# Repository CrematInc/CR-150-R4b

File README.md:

# CR-150-R4b
KiCad files for Cremat's CR-150-R4b, an evaluation board for Cremat's charge sensitive preamplifier modules CR-11X
Includes Schematic, layout, and gerber files. Also a BOM.

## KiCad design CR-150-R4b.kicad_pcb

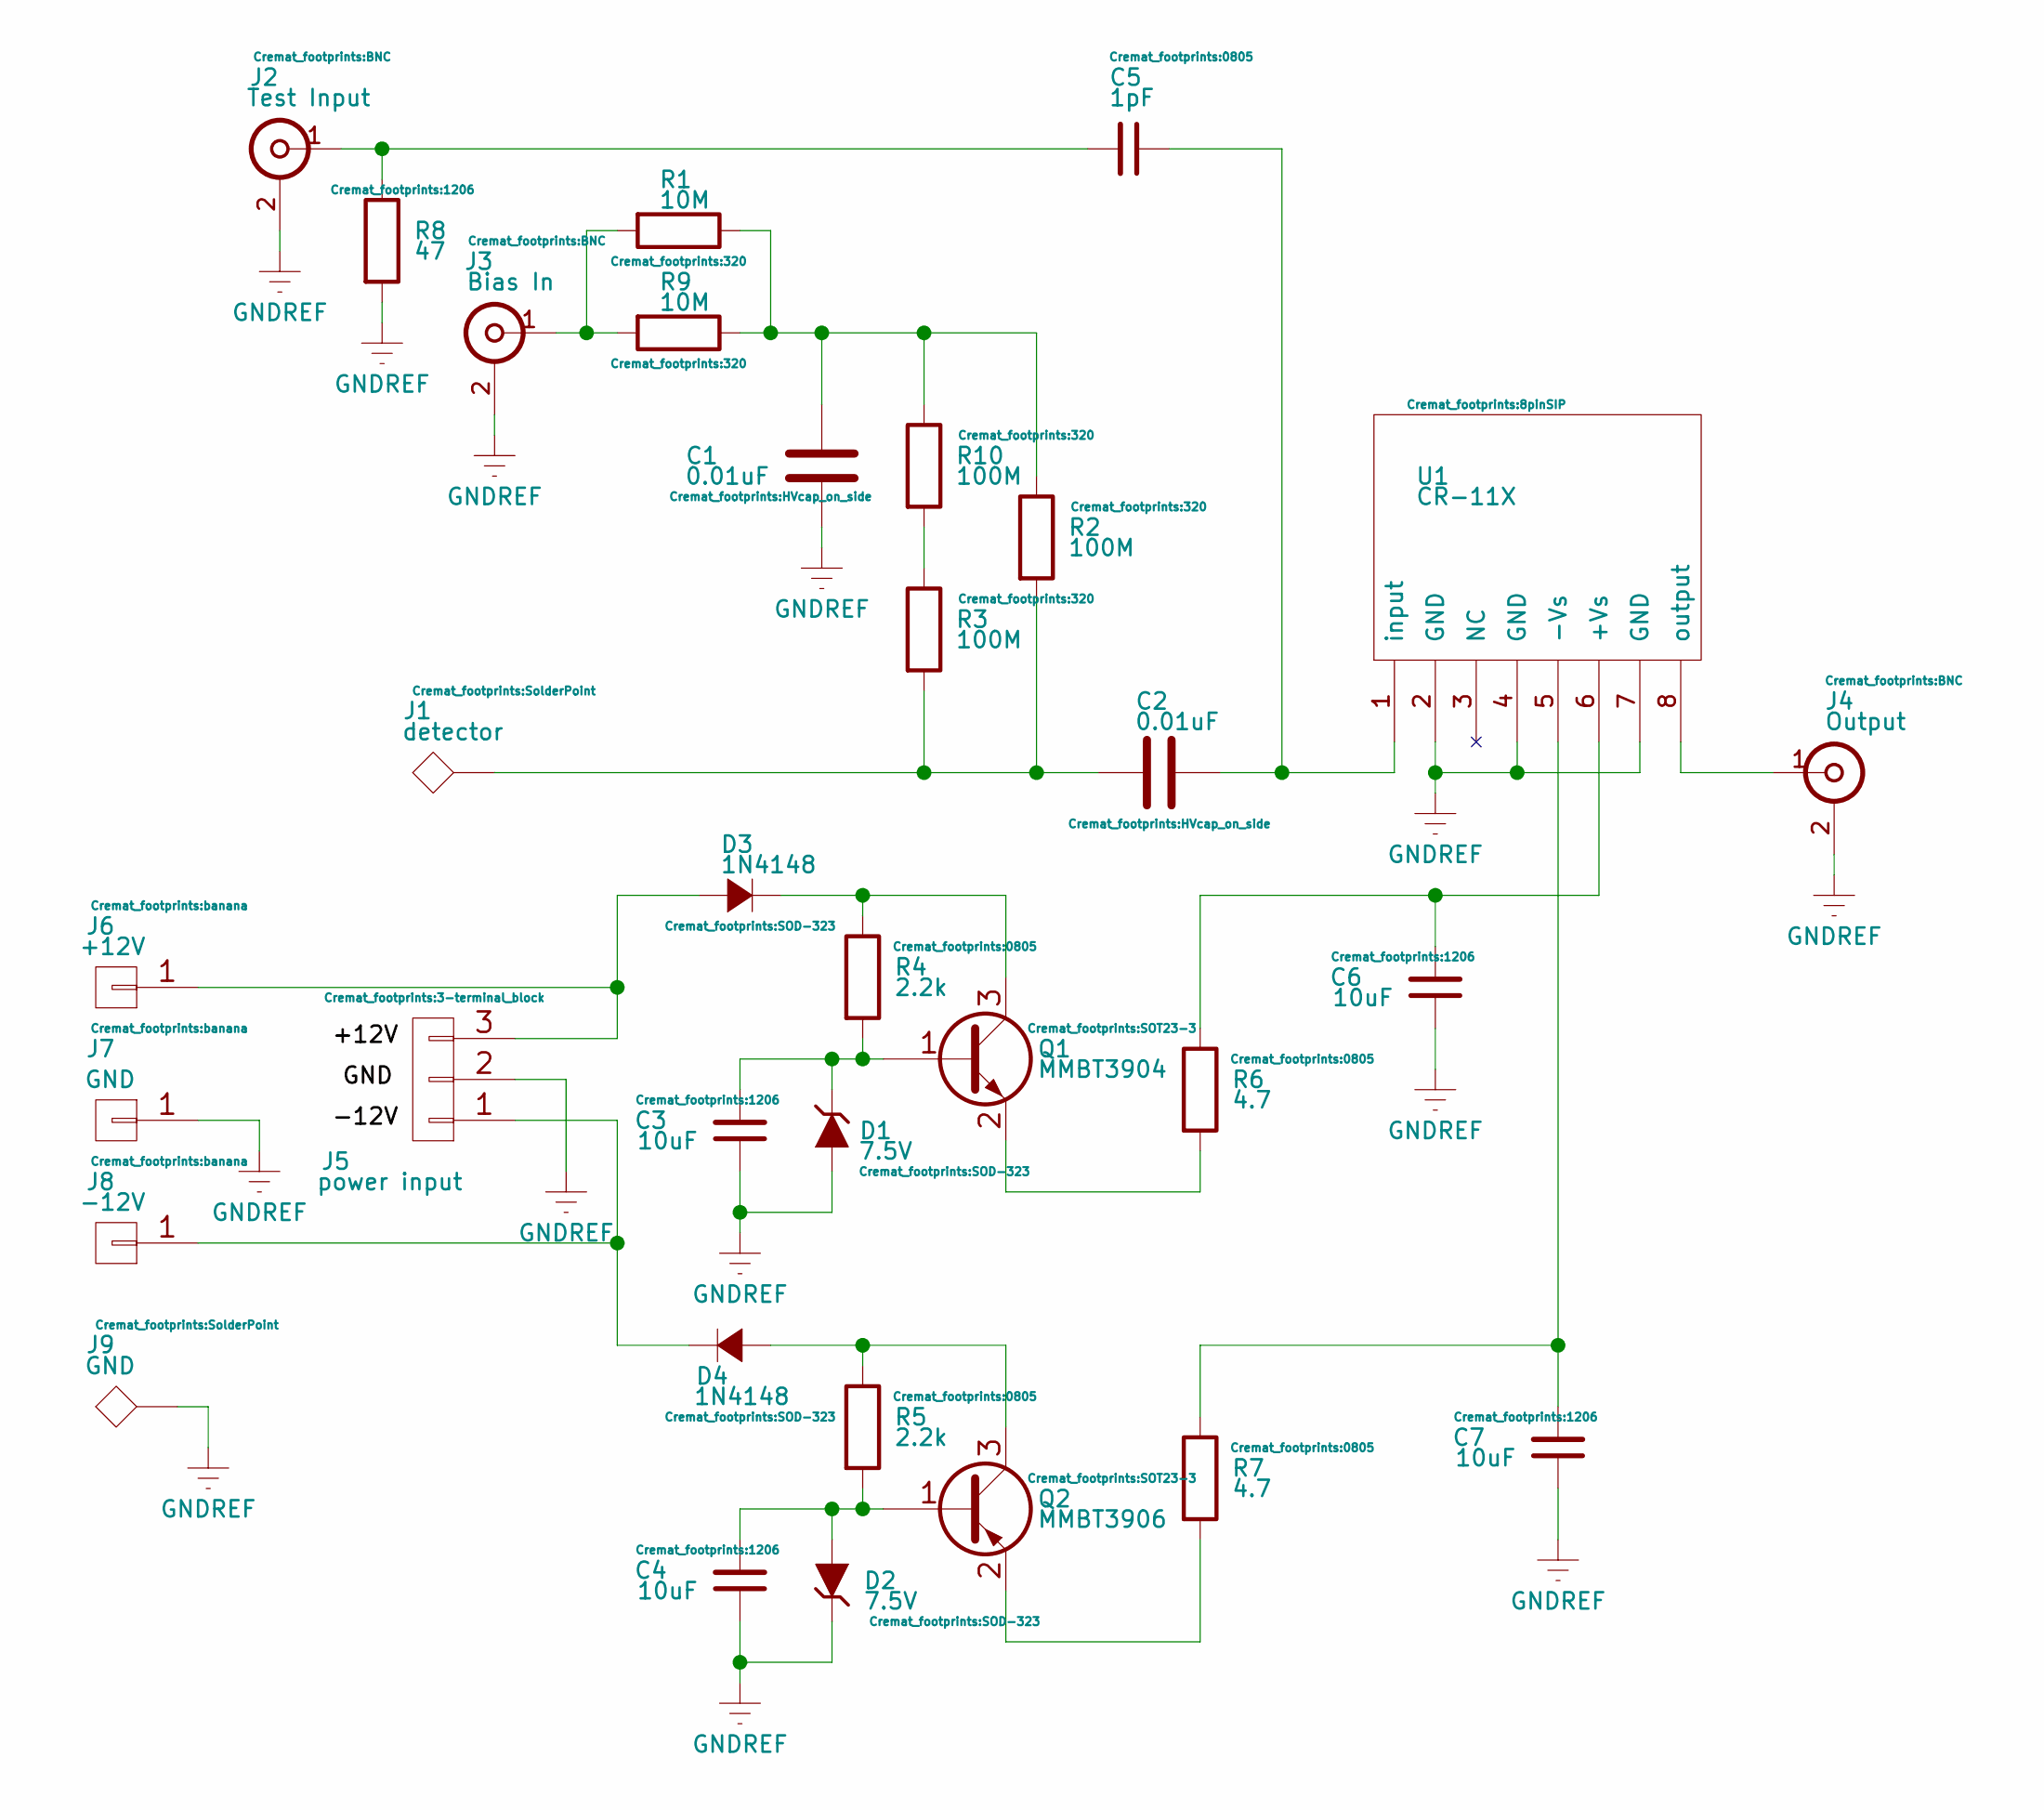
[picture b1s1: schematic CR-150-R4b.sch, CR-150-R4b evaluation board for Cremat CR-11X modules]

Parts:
C1, C2: 0.01uF; HVcap_on_side
C3, C4, C6, C7: 10uF; 1206
C5: 1pF; 0805
D1, D2: 7.5V; SOD-323
D3, D4: 1N4148; SOD-323
J1: detector; SolderPoint
J2: Test Input; BNC
J3: Bias In; BNC
J4: Output; BNC
J5: power input; 3-terminal_block
J6: +12V; banana
J7: GND; banana
J8: -12V; banana
J9: GND; SolderPoint
Q1: MMBT3904; SOT23-3
Q2: MMBT3906; SOT23-3
R1, R9: 10M; 320
R2, R3, R10: 100M; 320
R4, R5: 2.2k; 0805
R6, R7: 4.7; 0805
R8: 47; 1206
U1: CR-11X; 8pinSIP

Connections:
GNDREF: C1.1, C3.1, C4.1, C6.1, C7.1, D1.1 (A), D2.2 (K), J2.2 (Ext), J3.2 (Ext), J4.2 (Ext), J5.2, J7.1, J9.1, R8.2, U1.2 (GND), U1.4 (GND), U1.7 (GND)
unnamed: C1.2, R1.1, R2.1, R9.1, R10.1
unnamed: C2.1, J1.1, R2.2, R3.2
unnamed: C2.2, C5.1, U1.1 (input)
unnamed: C3.2, D1.2 (K), Q1.1 (B), R4.2
unnamed: C4.2, D2.1 (A), Q2.1 (B), R5.2
unnamed: C5.2, J2.1 (In), R8.1
unnamed: C6.2, R6.1, U1.6 (+Vs)
unnamed: C7.2, R7.1, U1.5 (-Vs)
unnamed: D3.1 (A), J5.3, J6.1
unnamed: D3.2 (C), Q1.3 (C), R4.1
unnamed: D4.1 (A), Q2.3 (C), R5.1
unnamed: D4.2 (C), J5.1, J8.1
unnamed: J3.1 (In), R1.2, R9.2
unnamed: J4.1 (In), U1.8 (output)
unnamed: Q1.2 (E), R6.2
unnamed: Q2.2 (E), R7.2
unnamed: R3.1, R10.2

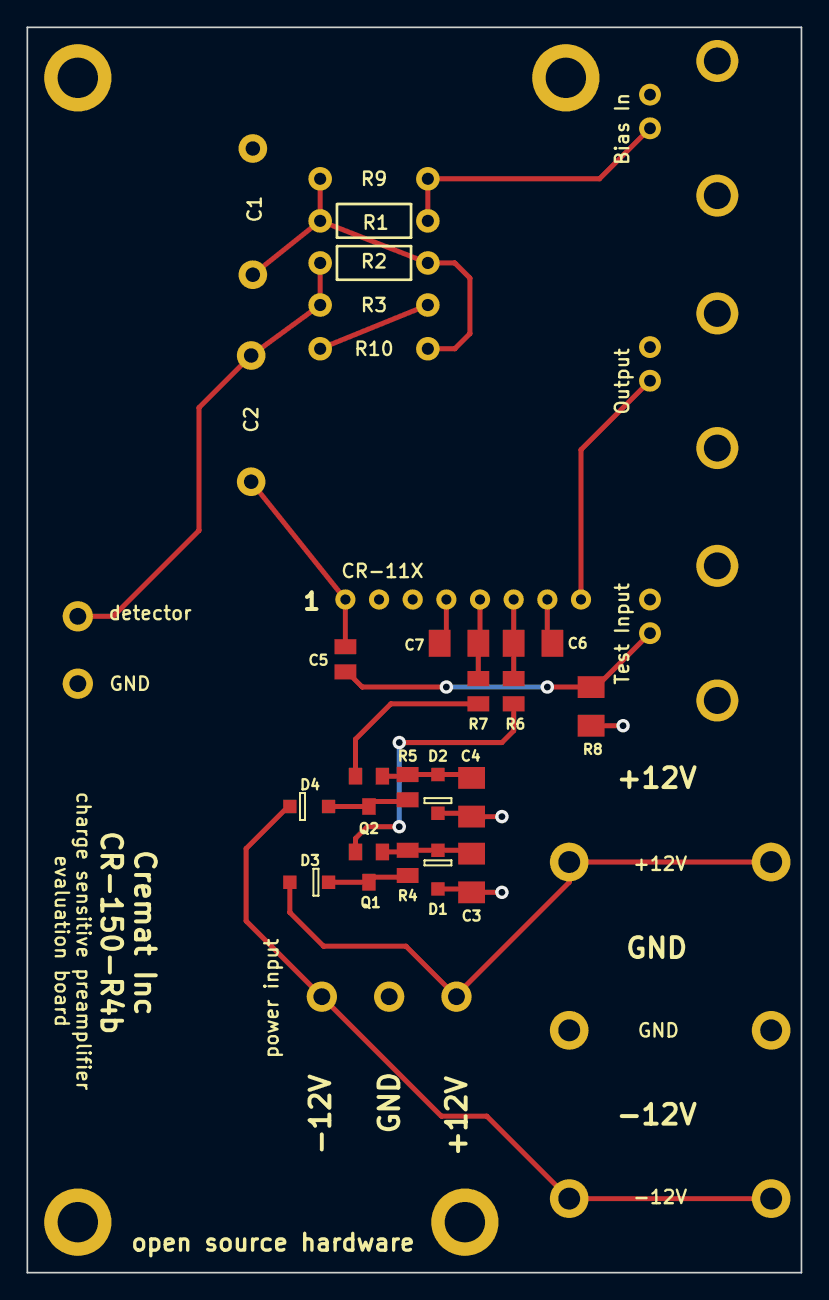
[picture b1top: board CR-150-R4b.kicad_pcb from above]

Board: 2 copper layers, 58.4 x 94.0 mm, 33 parts (0 on the bottom side), 18 nets.

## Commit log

2015-11-23 :boom::camel: Added .gitattributes & .gitignore files
2015-11-23 CR-150-R4b evaluation board for Cremat's charge sensitive preamplifier modules CR-11X
    KiCad files, Gerber files, bill of materials (BOM), schematic, layout
    image of CR-150-R4b

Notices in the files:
CR-150-R4b.sch:
This is Open Source Hardware under the MIT license. http://opensource.org/licenses/MIT
